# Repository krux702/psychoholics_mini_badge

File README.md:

# psychoholics_mini_badge

Board files and code for the Psychoholics Mini Badge

hardware - contains the EagleCAD schematics and board file
software - contains the Arduino code for the ATMega328p

Video demonstration

https://www.youtube.com/watch?v=WanU8pMmW9c

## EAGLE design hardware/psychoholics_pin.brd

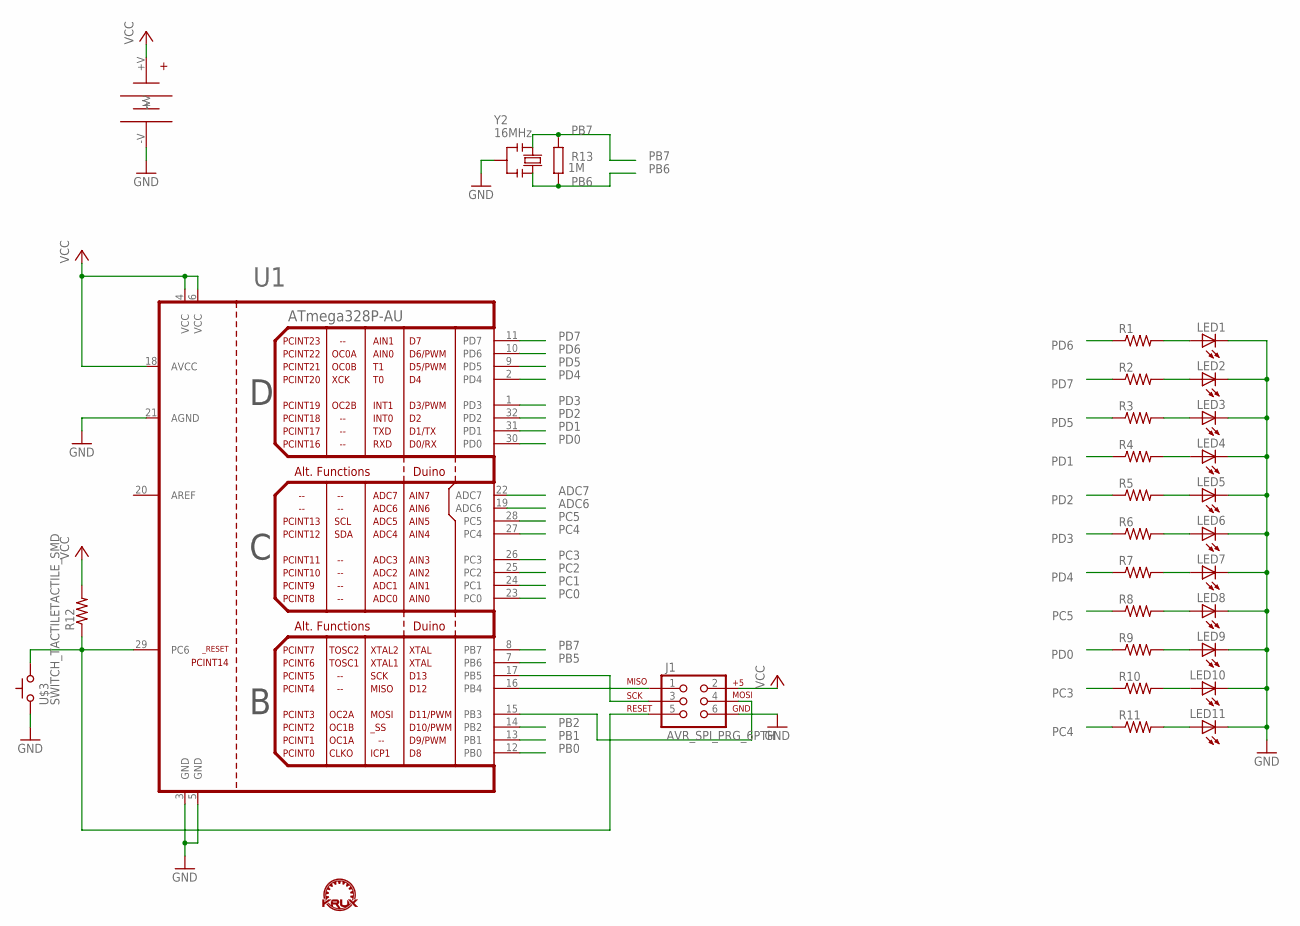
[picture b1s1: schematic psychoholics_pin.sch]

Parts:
J1: AVR_SPI_PRG_6PTH; 2X3
LED1, LED2, LED3, LED4, LED5, LED6, LED7, LED8, LED9, LED10, LED11: LEDREVERSEMOUNT; GULLWING_LED
R1, R2, R3, R4, R5, R6, R7, R8, R9, R10, R11, R12: RESISTOR0603-RES; 0603-RES
R13: 1M; R0603-ROUND
U1: ATmega328P-AU; TQFP-32-08-THIN
U$1: KRUX_LOGO
U$2: 12BH423-GR12BH423-GR_NOBORDER; 12BH423-GR_NOBORDER
U$3: SWITCH_TACTILETACTILE_SMD; TACTILE_SWITCH_SMD
Y2: 16MHz; RESONATOR

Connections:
ADC6: U1.19 (ADC6)
ADC7: U1.22 (ADC7)
GND: J1.6, LED1.C, LED2.C, LED3.C, LED4.C, LED5.C, LED6.C, LED7.C, LED8.C, LED9.C, LED10.C, LED11.C, U1.3 (GND), U1.5 (GND), U1.21 (AGND), U$2.-V, U$3.3 (C), U$3.4 (C), Y2.2
unnamed: LED11.A, R11.2
unnamed: LED10.A, R10.2
unnamed: LED9.A, R9.2
unnamed: LED8.A, R8.2
unnamed: LED7.A, R7.2
unnamed: LED6.A, R6.2
unnamed: LED5.A, R5.2
unnamed: LED4.A, R4.2
unnamed: LED3.A, R3.2
unnamed: LED2.A, R2.2
unnamed: LED1.A, R1.2
unnamed: J1.5, R12.1, U1.29 (PC6), U$3.1 (A), U$3.2 (A)
PB0: U1.12 (PB0)
PB1: U1.13 (PB1)
PB2: U1.14 (PB2)
PB3: J1.4, U1.15 (PB3)
PB4: J1.1, U1.16 (PB4)
PB5: J1.3, U1.17 (PB5)
PB6: R13.1, U1.7 (PB6), Y2.3
PB7: R13.2, U1.8 (PB7), Y2.1
PC0: U1.23 (PC0)
PC1: U1.24 (PC1)
PC2: U1.25 (PC2)
PC3: R10.1, U1.26 (PC3)
PC4: R11.1, U1.27 (PC4)
PC5: R8.1, U1.28 (PC5)
PD0: R9.1, U1.30 (PD0)
PD1: R4.1, U1.31 (PD1)
PD2: R5.1, U1.32 (PD2)
PD3: R6.1, U1.1 (PD3)
PD4: R7.1, U1.2 (PD4)
PD5: R3.1, U1.9 (PD5)
PD6: R1.1, U1.10 (PD6)
PD7: R2.1, U1.11 (PD7)
VCC: J1.2, R12.2, U1.4 (VCC), U1.6 (VCC), U1.18 (AVCC), U$2.+V

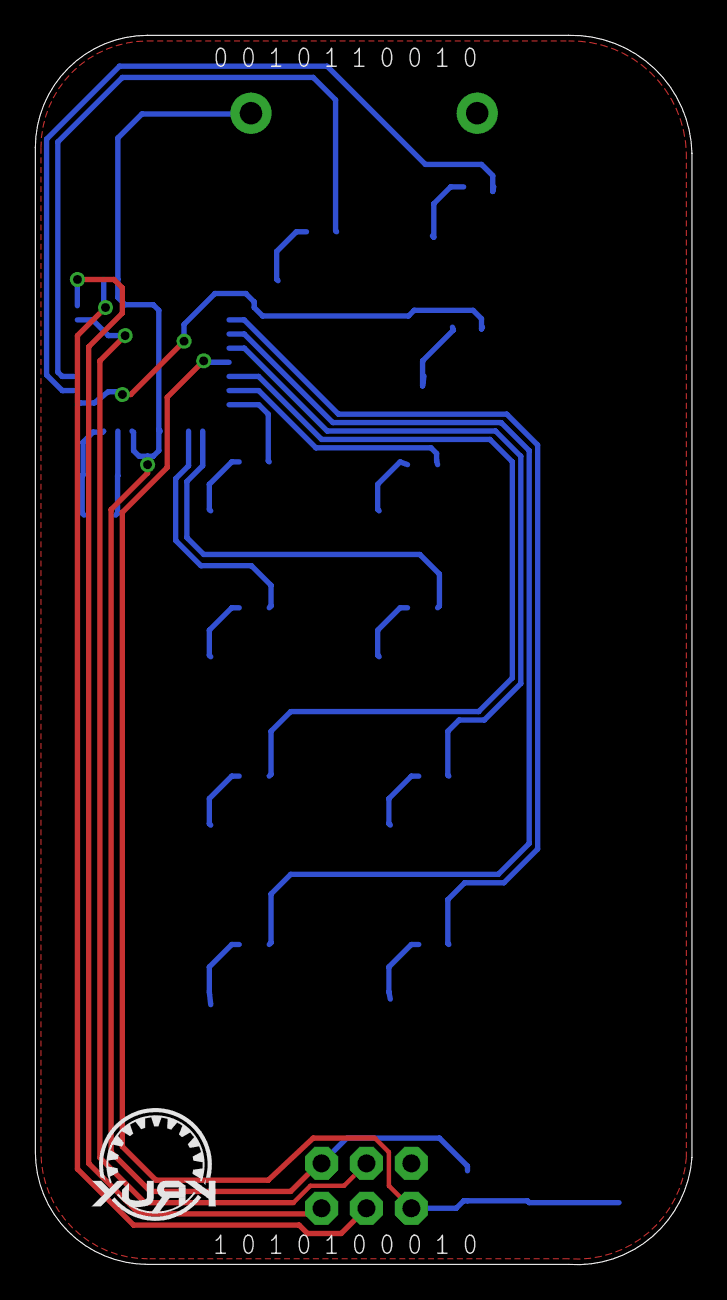
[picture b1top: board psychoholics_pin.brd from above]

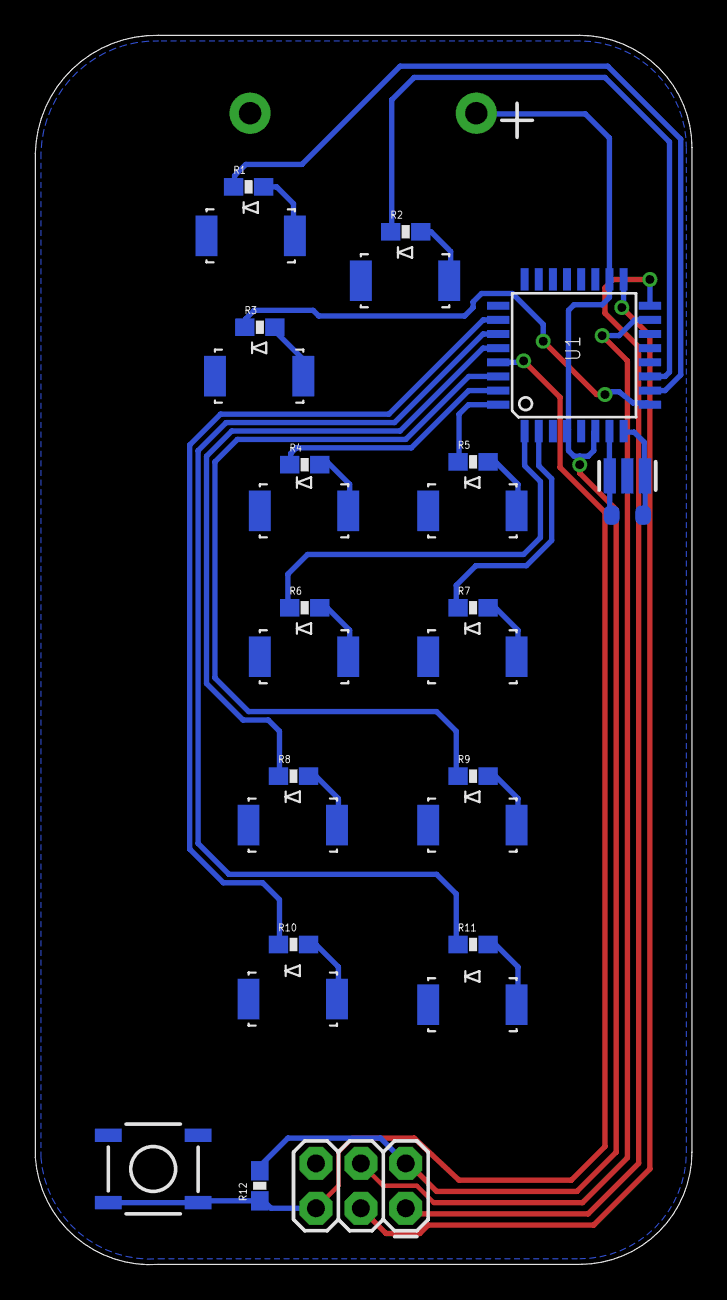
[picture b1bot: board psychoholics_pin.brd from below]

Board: 2 copper layers, 37.1 x 69.5 mm, 30 parts (29 on the bottom side), 30 nets.

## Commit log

2021-11-18 Added hardware and software
2021-11-18 Added video

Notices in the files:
parts and their libraries:
SparkFun: Licensing: CC v3.0 Share-Alike You are welcome to use this library for commercial purposes.
